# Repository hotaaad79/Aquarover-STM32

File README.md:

# Aquarover-STM32
# Aquarover Surface-Driving Robot using STM32

## Overview

The Aquarover Surface-Driving Robot is a floating robotic system designed to move across the water surface. The robot is controlled using an STM32 microcontroller and allows manual control using a joystick 
This project was completed during the Aquarover Workshop at DeepTech Club and demonstrates embedded systems, motor control, and PCB design skills.

## Hardware Components

- STM32 Blue Pill Microcontroller
- Thruster DC Motors
- Servo Motor
- L298N Motor Driver
- Joystick Module
- Potentiometers
- Step-Down Converter (5V)
- Battery and Power Module
- Perfboard (Donut Board)
- Connecting Wires

---

## Software Tools

- STM32CubeIDE
- Embedded C Language
- STM32 HAL Libraries

---

## System Operation

- Joystick provides analog input
- STM32 reads input using ADC
- STM32 generates PWM signals
- Motor driver controls thruster motors
- Robot moves forward, backward, left, and right on water surface

---

## Hardware Implementation

The complete circuit was soldered on a perfboard (donut board) to ensure stable and reliable operation.

---

## PCB Design

A custom PCB was designed using KiCad to demonstrate professional circuit layout.  
However, the PCB was not fabricated.

---

## Results

- Robot successfully moved on water surface
- Smooth and accurate motor control
- Stable hardware operation
- Successful integration of embedded system and motor control

---

## Future Improvements

- Add wireless control (Bluetooth / WiFi)
- Manufacture PCB
- Add autonomous navigation
- Add sensors for obstacle detection
## Author

Mohamed Abdelnabi 
Electrical Engineering Student

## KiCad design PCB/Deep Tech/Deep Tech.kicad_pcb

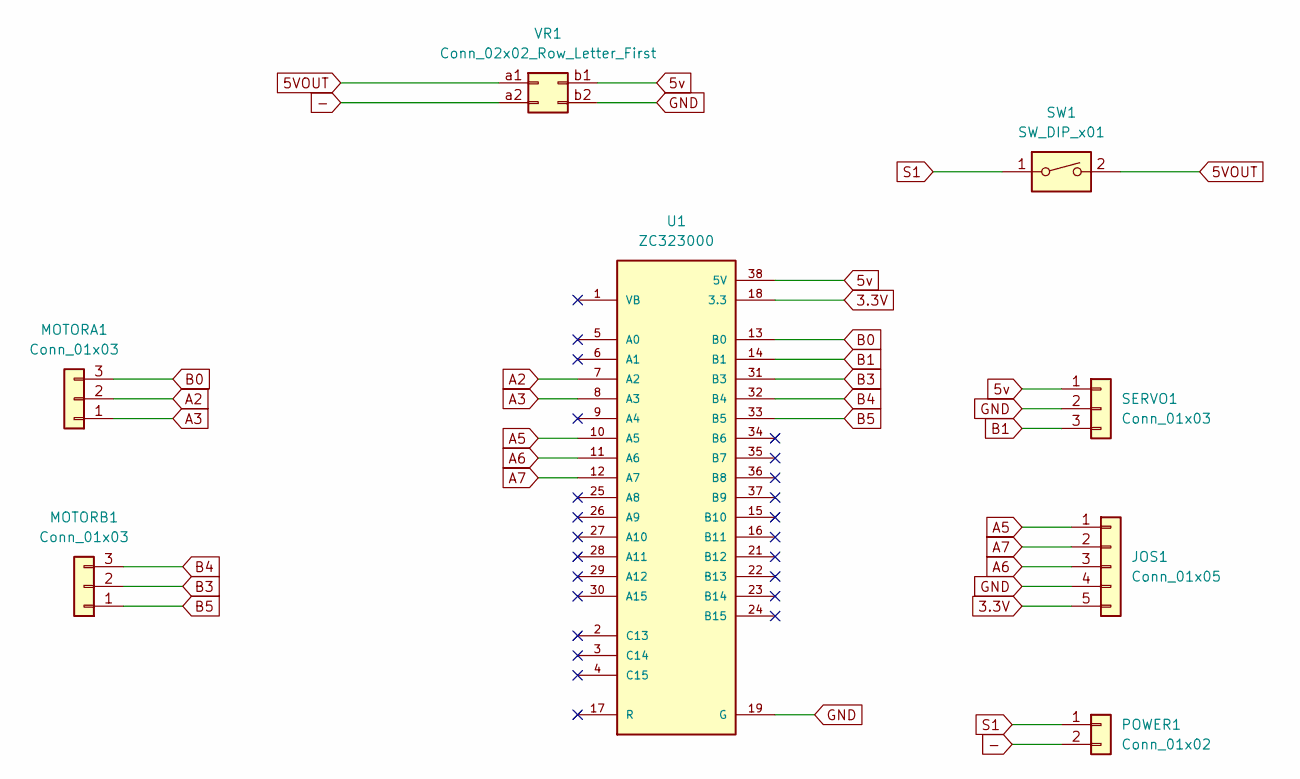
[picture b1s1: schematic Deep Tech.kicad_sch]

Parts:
JOS1: Conn_01x05; PinHeader_1x05_P2.54mm_Vertical
MOTORA1: Conn_01x03; PinHeader_1x03_P2.54mm_Vertical
MOTORB1: Conn_01x03; PinHeader_1x03_P2.54mm_Vertical
POWER1: Conn_01x02; TerminalBlock_Xinya_XY308-2.54-2P_1x02_P2.54mm_Horizontal
SERVO1: Conn_01x03; PinHeader_1x03_P2.54mm_Vertical
SW1: SW_DIP_x01; SW_Slide-03_Wuerth-WS-SLTV_10x2.5x6.4_P2.54mm
U1: ZC323000; MODULE_ZC323000; PARTREV N/A
VR1: Conn_02x02_Row_Letter_First; Untitled

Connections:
3.3V: JOS1.5, U1.18 (3.3), U1.40 (3.3)
5VOUT: SW1.2, VR1.a1
5v: SERVO1.1, U1.38 (5V), VR1.b1
-: POWER1.2, VR1.a2
A2: MOTORA1.2, U1.7 (A2)
A3: MOTORA1.1, U1.8 (A3)
A5: JOS1.1, U1.10 (A5)
A6: JOS1.3, U1.11 (A6)
A7: JOS1.2, U1.12 (A7)
B0: MOTORA1.3, U1.13 (B0)
B1: SERVO1.3, U1.14 (B1)
B3: MOTORB1.2, U1.31 (B3)
B4: MOTORB1.3, U1.32 (B4)
B5: MOTORB1.1, U1.33 (B5)
GND: JOS1.4, SERVO1.2, U1.19 (G), U1.20 (G), U1.39 (G), VR1.b2
S1: POWER1.1, SW1.1

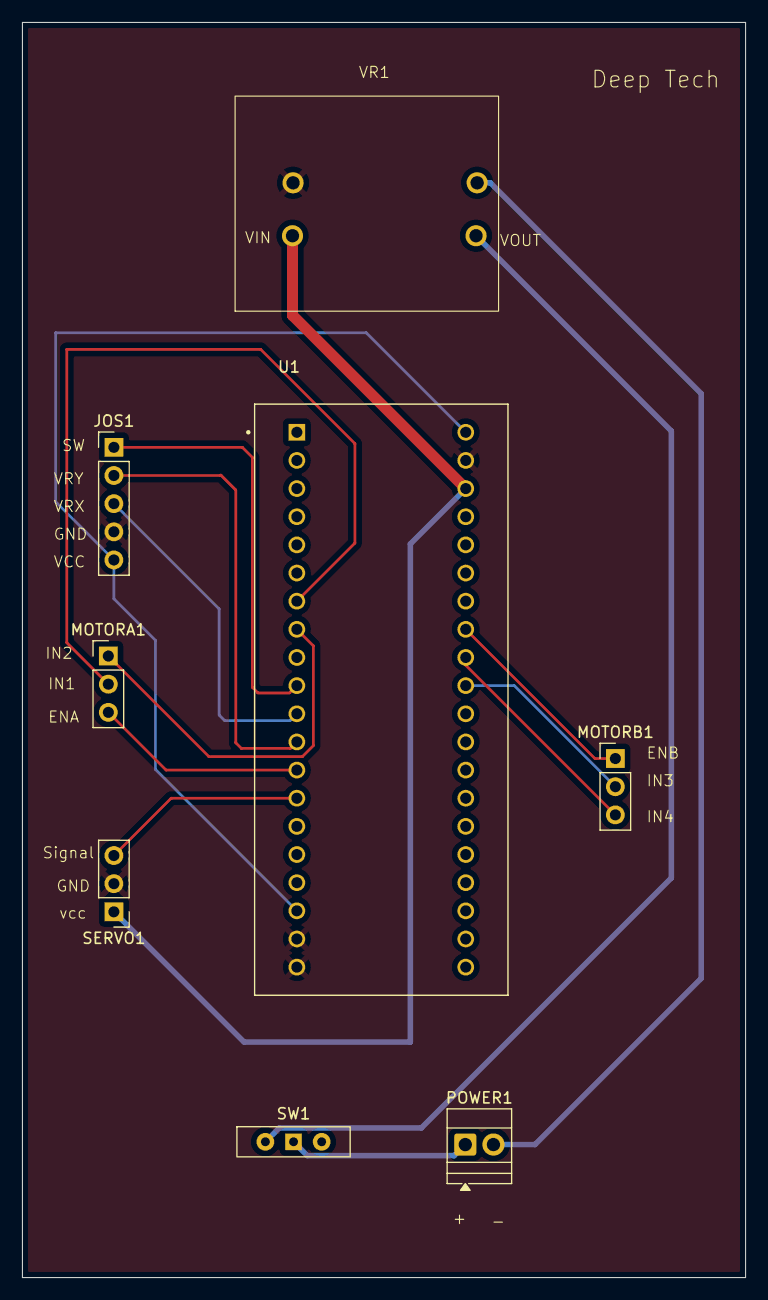
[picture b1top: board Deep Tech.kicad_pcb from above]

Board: 2 copper layers, 65.2 x 113.2 mm, 8 parts (0 on the bottom side), 16 nets.
